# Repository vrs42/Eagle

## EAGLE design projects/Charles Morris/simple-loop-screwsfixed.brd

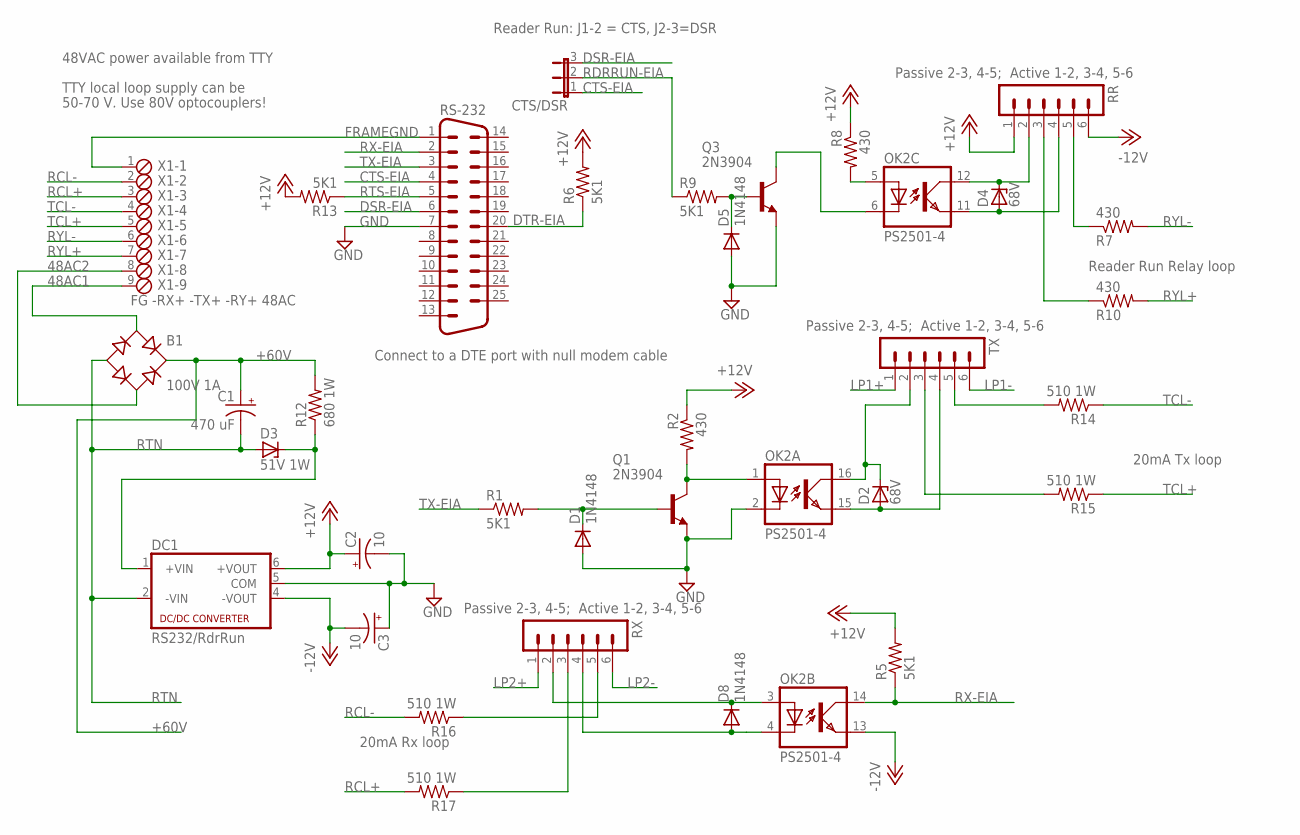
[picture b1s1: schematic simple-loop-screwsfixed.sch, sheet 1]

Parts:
B1: 100V 1A; RB1A
C1: 470 uF; E7,5-18
C2, C3: 10; B45181A
CTS/DSR: JP2E; JP2
D1, D5, D8: 1N4148; DO35-10
D2, D4: 68V; DO41Z10
D3: 51V 1W; DO41Z10
DC1: RS232/RdrRun; NMA
OK2: PS2501-4; DIL16
Q1, Q3: 2N3904; TO92
R1, R5, R6, R9, R13: 5K1; 0207/10
R2, R7, R8, R10: 430; 0207/10
R12: 680 1W; P0817V
R14, R15, R16, R17: 510 1W; P0817V
RR: MA06-1
RS-232: M25H
RX: MA06-1
TX: MA06-1
X1: FG -RX+ -TX+ -RY+ 48AC; 9POL254

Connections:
48AC1: B1.AC1, X1.9
48AC2: B1.AC2, X1.8
+12V: C2.+, DC1.6 (+VOUT), R2.1, R5.2, R6.2, R8.1, R13.2, RR.1
+48VDC: D3.C, DC1.1 (+VIN), R12.1
+60V: B1.+, C1.+, R12.2; also elsewhere on the board
-12V: C3.-, DC1.4 (-VOUT), OK2.13 (EMIT), RR.6
CTS-EIA: CTS/DSR.1, RS-232.4
DSR-EIA: CTS/DSR.3, RS-232.6
DTR-EIA: R6.1, RS-232.20
FRAMEGND: RS-232.1, X1.1
GND: C2.-, C3.+, D1.A, D5.A, DC1.5 (COM), OK2.2 (C), Q1.3 (E), Q3.3 (E), RS-232.7
LP1+: TX.1; also elsewhere on the board
LP1-: TX.6; also elsewhere on the board
LP2+: RX.1; also elsewhere on the board
LP2-: RX.6; also elsewhere on the board
unnamed: D8.C, OK2.3 (A), RX.2
unnamed: R16.1, RX.5
unnamed: D8.A, OK2.4 (C), RX.4
unnamed: D2.A, OK2.15 (EMIT), TX.4
unnamed: OK2.5 (A), R8.2
unnamed: D2.C, OK2.16 (COL), TX.2
unnamed: D1.C, Q1.2 (B), R1.2
unnamed: D4.C, OK2.12 (COL), RR.2
unnamed: OK2.1 (A), Q1.1 (C), R2.2
unnamed: R10.1, RR.3
unnamed: R7.1, RR.5
unnamed: OK2.6 (C), Q3.1 (C)
unnamed: D5.C, Q3.2 (B), R9.2
unnamed: R14.2, TX.5
unnamed: R17.1, RX.3
unnamed: R15.2, TX.3
unnamed: D4.A, OK2.11 (EMIT), RR.4
RCL+: R17.2, X1.3
RCL-: R16.2, X1.2
RDRRUN-EIA: CTS/DSR.2, R9.1
RTN: B1.-, C1.-, D3.A, DC1.2 (-VIN); also elsewhere on the board
RTS-EIA: R13.1, RS-232.5
RX-EIA: OK2.14 (COL), R5.1, RS-232.2
RYL+: R10.2, X1.7
RYL-: R7.2, X1.6
TCL+: R15.1, X1.5
TCL-: R14.1, X1.4
TX-EIA: R1.1, RS-232.3

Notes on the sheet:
TTY local loop supply can be
50-70 V. Use 80V optocouplers!
20mA Tx loop
20mA Rx loop
48VAC power available from TTY
Reader Run Relay loop
Connect to a DTE port with null modem cable
Passive 2-3, 4-5; Active 1-2, 3-4, 5-6
Reader Run: J1-2 = CTS, J2-3=DSR

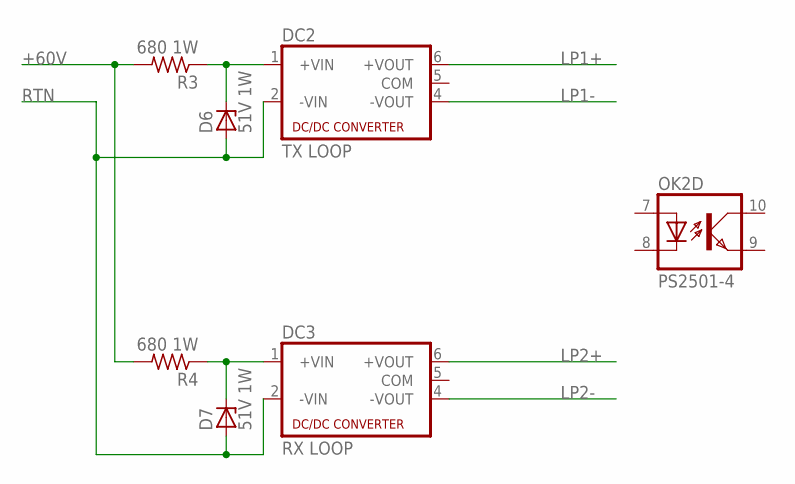
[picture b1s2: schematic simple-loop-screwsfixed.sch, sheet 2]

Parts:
D6, D7: 51V 1W; DO41Z10
DC2: TX LOOP; NMA
DC3: RX LOOP; NMA
OK2: PS2501-4; DIL16
R3, R4: 680 1W; P0817V

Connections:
+48VDC1: D6.C, DC2.1 (+VIN), R3.1
+48VDC2: D7.C, DC3.1 (+VIN), R4.1
+60V: R3.2, R4.2; also elsewhere on the board
LP1+: DC2.6 (+VOUT); also elsewhere on the board
LP1-: DC2.4 (-VOUT); also elsewhere on the board
LP2+: DC3.6 (+VOUT); also elsewhere on the board
LP2-: DC3.4 (-VOUT); also elsewhere on the board
RTN: D6.A, D7.A, DC2.2 (-VIN), DC3.2 (-VIN); also elsewhere on the board

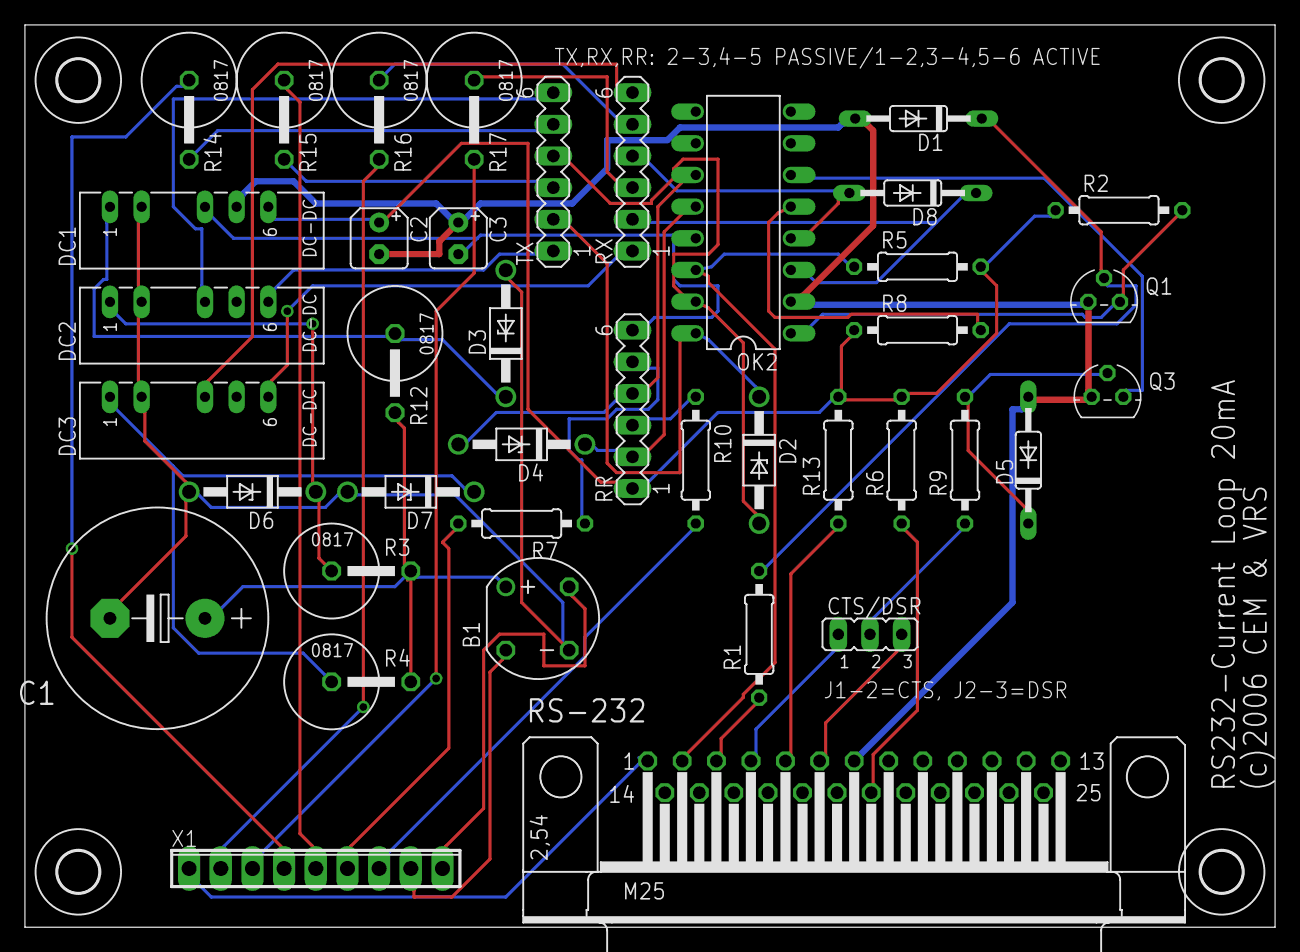
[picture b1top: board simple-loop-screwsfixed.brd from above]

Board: 2 copper layers, 100.3 x 72.4 mm, 44 parts (0 on the bottom side), 45 nets.

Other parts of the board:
U$1, U$2, U$3, U$4: 3,3

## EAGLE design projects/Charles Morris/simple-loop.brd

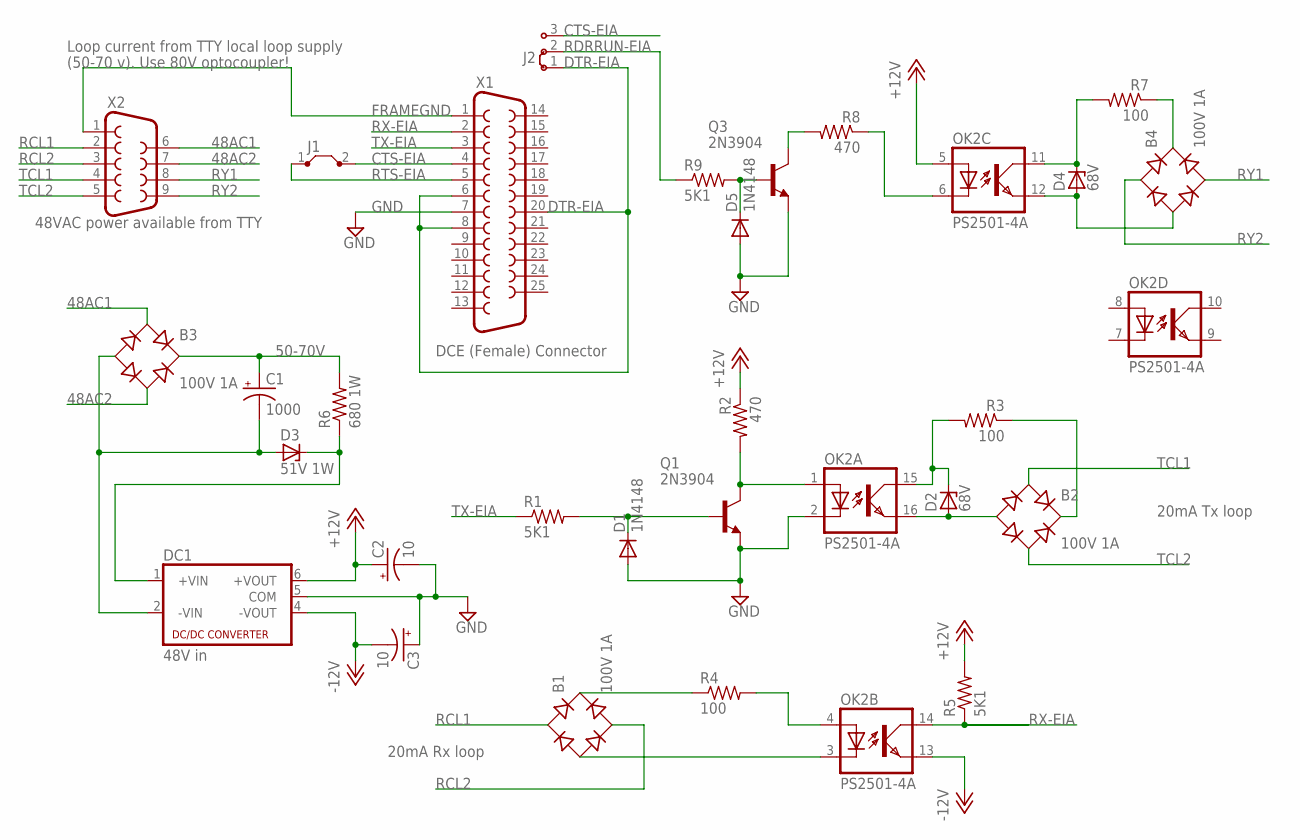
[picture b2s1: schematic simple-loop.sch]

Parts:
B1, B2, B3, B4: 100V 1A; RB1A
C1: 1000; E7,5-18
C2, C3: 10; B45181A
D1, D5: 1N4148; DO35-10
D2, D4: 68V; DO41Z10
D3: 51V 1W; DO41Z10
DC1: 48V in; NMA
J1: J5MM; 05
J2: J2X5MM; 05C
OK2: PS2501-4A; DIL16
Q1, Q3: 2N3904; TO92
R1, R5, R9: 5K1; 0207/10
R2, R8: 470; 0207/10
R3, R4, R7: 100; 0207/10
R6: 680 1W; 0617/17
X1: F25H
X2: F09H

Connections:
48AC1: B3.AC1, X2.6
48AC2: B3.AC2, X2.7
50-70V: B3.+, C1.+, R6.2
+12V: C2.+, DC1.6 (+VOUT), OK2.5 (A), R2.1, R5.2
-12V: C3.-, DC1.4 (-VOUT), OK2.13 (EMIT)
CTS-EIA: J1.2, J2.3, X1.4
DTR-EIA: J2.1, X1.6, X1.8, X1.20
FRAMEGND: X1.1, X2.1
GND: C2.-, C3.+, D1.A, D5.A, DC1.5 (COM), OK2.2 (C), Q1.3 (E), Q3.3 (E), X1.7
unnamed: OK2.4 (A), R4.2
unnamed: B1.+, R4.1
unnamed: B1.-, OK2.3 (C)
unnamed: B2.-, D2.A, OK2.16 (EMIT)
unnamed: B2.+, R3.1
unnamed: D2.C, OK2.15 (COL), R3.2
unnamed: D1.C, Q1.2 (B), R1.2
unnamed: D3.C, DC1.1 (+VIN), R6.1
unnamed: OK2.1 (A), Q1.1 (C), R2.2
unnamed: B3.-, C1.-, D3.A, DC1.2 (-VIN)
unnamed: D4.C, OK2.11 (COL), R7.2
unnamed: B4.-, D4.A, OK2.12 (EMIT)
unnamed: B4.+, R7.1
unnamed: OK2.6 (C), R8.1
unnamed: D5.C, Q3.2 (B), R9.2
unnamed: Q3.1 (C), R8.2
RCL1: B1.AC1, X2.2
RCL2: B1.AC2, X2.3
RDRRUN-EIA: J2.2, R9.1
RTS-EIA: J1.1, X1.5
RX-EIA: OK2.14 (COL), R5.1, X1.2
RY1: B4.AC2, X2.8
RY2: B4.AC1, X2.9
TCL1: B2.AC1, X2.4
TCL2: B2.AC2, X2.5
TX-EIA: R1.1, X1.3

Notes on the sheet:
DCE (Female) Connector
Loop current from TTY local loop supply
(50-70 v). Use 80V optocoupler!
20mA Tx loop
20mA Rx loop
48VAC power available from TTY

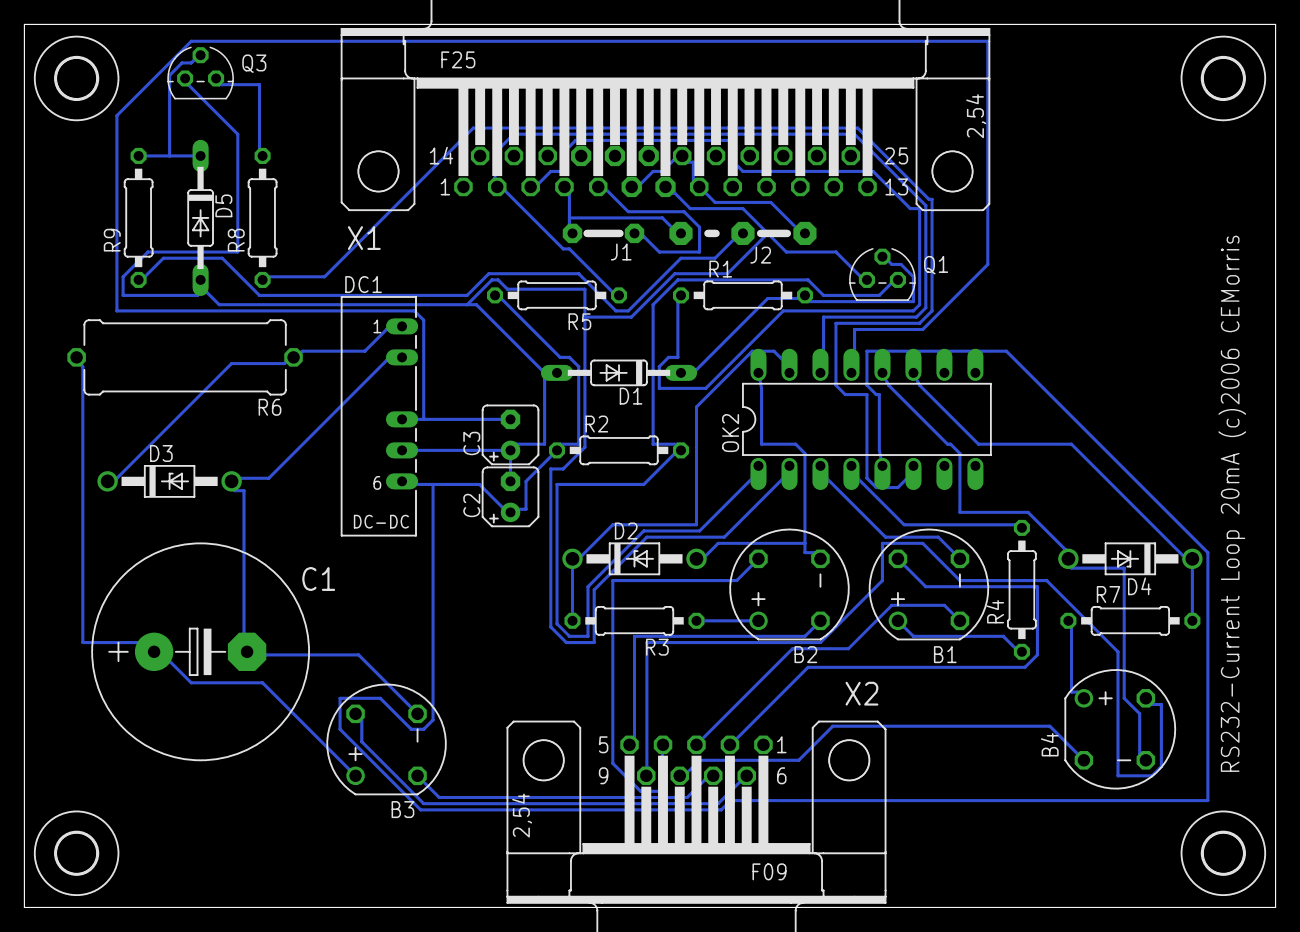
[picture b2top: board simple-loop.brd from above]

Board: 2 copper layers, 102.5 x 72.4 mm, 33 parts (0 on the bottom side), 35 nets.

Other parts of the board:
U$1, U$2, U$3, U$4: 3,3

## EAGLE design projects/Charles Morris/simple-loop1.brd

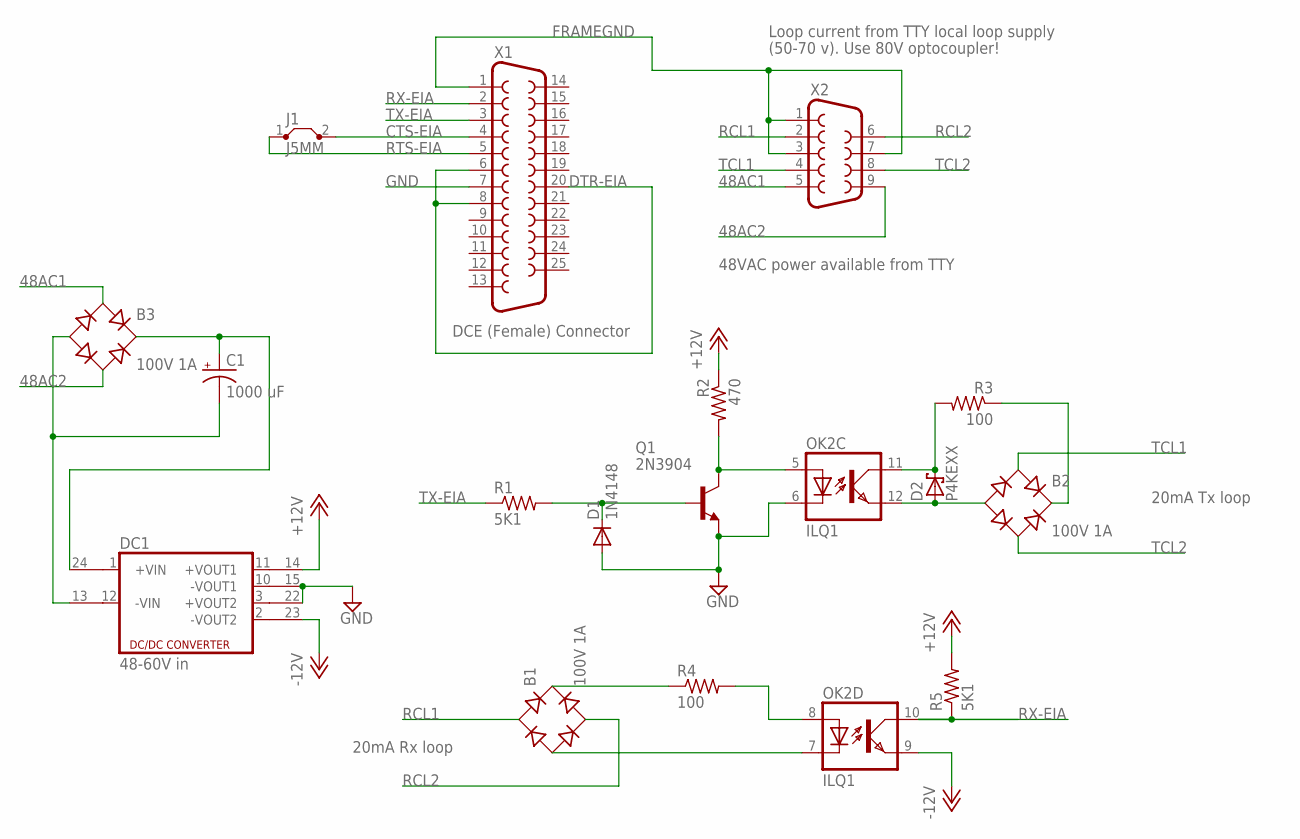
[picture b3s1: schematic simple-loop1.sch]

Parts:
B1, B2, B3: 100V 1A; RB1A
C1: 1000 uF; E7,5-18
D1: 1N4148; DO35-10
D2: P4KEXX; DO41-10
DC1: 48-60V in; DCW
J1: J5MM; 05
OK2: ILQ1; DIL16
Q1: 2N3904; TO92
R1, R5: 5K1; 0207/10
R2: 470; 0207/10
R3, R4: 100; 0207/10
X1: F25H
X2: F09H

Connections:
48AC1: B3.AC1, X2.5
48AC2: B3.AC2, X2.9
+12V: DC1.14 (+VOUT), R2.1, R5.2
-12V: DC1.23 (-VOUT), OK2.9 (EMIT)
CTS-EIA: J1.2, X1.4
DTR-EIA: X1.6, X1.8, X1.20
FRAMEGND: X1.1, X2.1, X2.3, X2.7
GND: D1.A, DC1.15 (-VOUT), DC1.22 (+VOUT), OK2.6 (C), Q1.3 (E), X1.7
unnamed: OK2.8 (A), R4.2
unnamed: B1.+, R4.1
unnamed: B1.-, OK2.7 (C)
unnamed: B2.-, D2.A, OK2.12 (EMIT)
unnamed: B2.+, R3.1
unnamed: D2.C, OK2.11 (COL), R3.2
unnamed: D1.C, Q1.2 (B), R1.2
unnamed: B3.+, C1.+, DC1.24 (+VIN1)
unnamed: OK2.5 (A), Q1.1 (C), R2.2
unnamed: B3.-, C1.-, DC1.13 (-VIN1)
RCL1: B1.AC1, X2.2
RCL2: B1.AC2, X2.6
RTS-EIA: J1.1, X1.5
RX-EIA: OK2.10 (COL), R5.1, X1.2
TCL1: B2.AC1, X2.4
TCL2: B2.AC2, X2.8
TX-EIA: R1.1, X1.3

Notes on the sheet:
DCE (Female) Connector
Loop current from TTY local loop supply
(50-70 v). Use 80V optocoupler!
20mA Tx loop
20mA Rx loop
48VAC power available from TTY

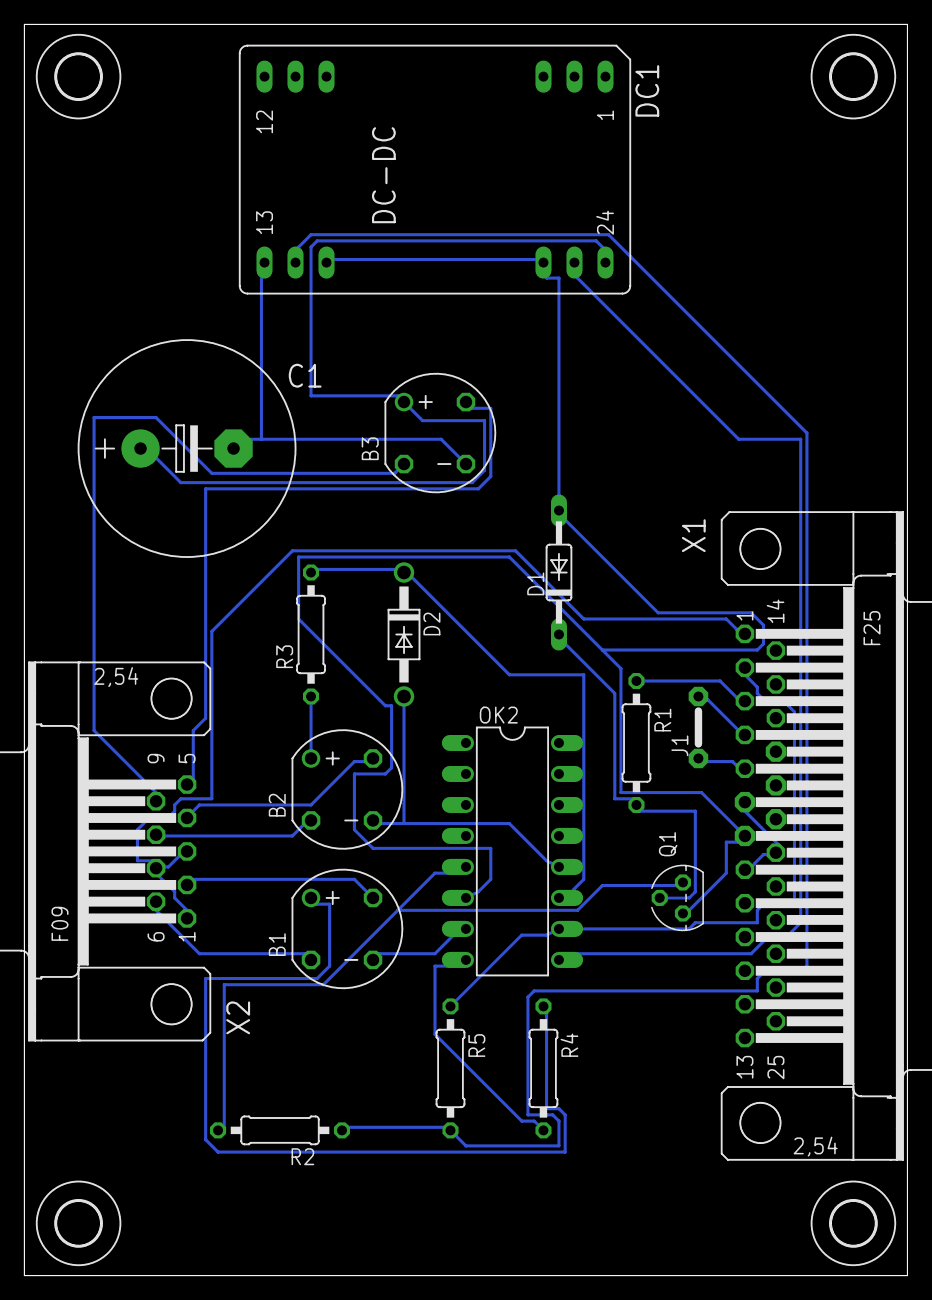
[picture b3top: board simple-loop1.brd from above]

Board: 2 copper layers, 72.4 x 102.5 mm, 21 parts (0 on the bottom side), 25 nets.

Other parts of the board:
U$1, U$2, U$3, U$4: 3,6

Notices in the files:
projects/Charles Morris/simple-loop-screwsfixed.brd:
(c)2006 CEM & VRS
projects/Charles Morris/simple-loop.brd:
RS232-Current Loop 20mA (c)2006 CEMorris
